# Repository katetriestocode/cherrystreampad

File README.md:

# cherrystreampad
hackclub project!

This is my cherrystreampad!
(cherry when i paint it LOL)
its used as a streampad/deck, with handy dandy tools such as volume control and app shortcuts!
I made this caus stream decks are super expensive, and this was so fun to do!!!

It has 6 keys, and OLED teeny screen and a rotary encoder!

# This is the PCB:

# And this is the schematic:

# this is (just) the case: 

# BOM parts

- 6x Cherry MX Switches
- 6x White Keycaps
- 4x M3x16mm screws
- 1x 0.91" 128x32 OLED Display
- 1x EC11 Rotary Encoder
- 1x XIAO RP2040
- 1x Case (2 printed parts)

<shark missing :(>

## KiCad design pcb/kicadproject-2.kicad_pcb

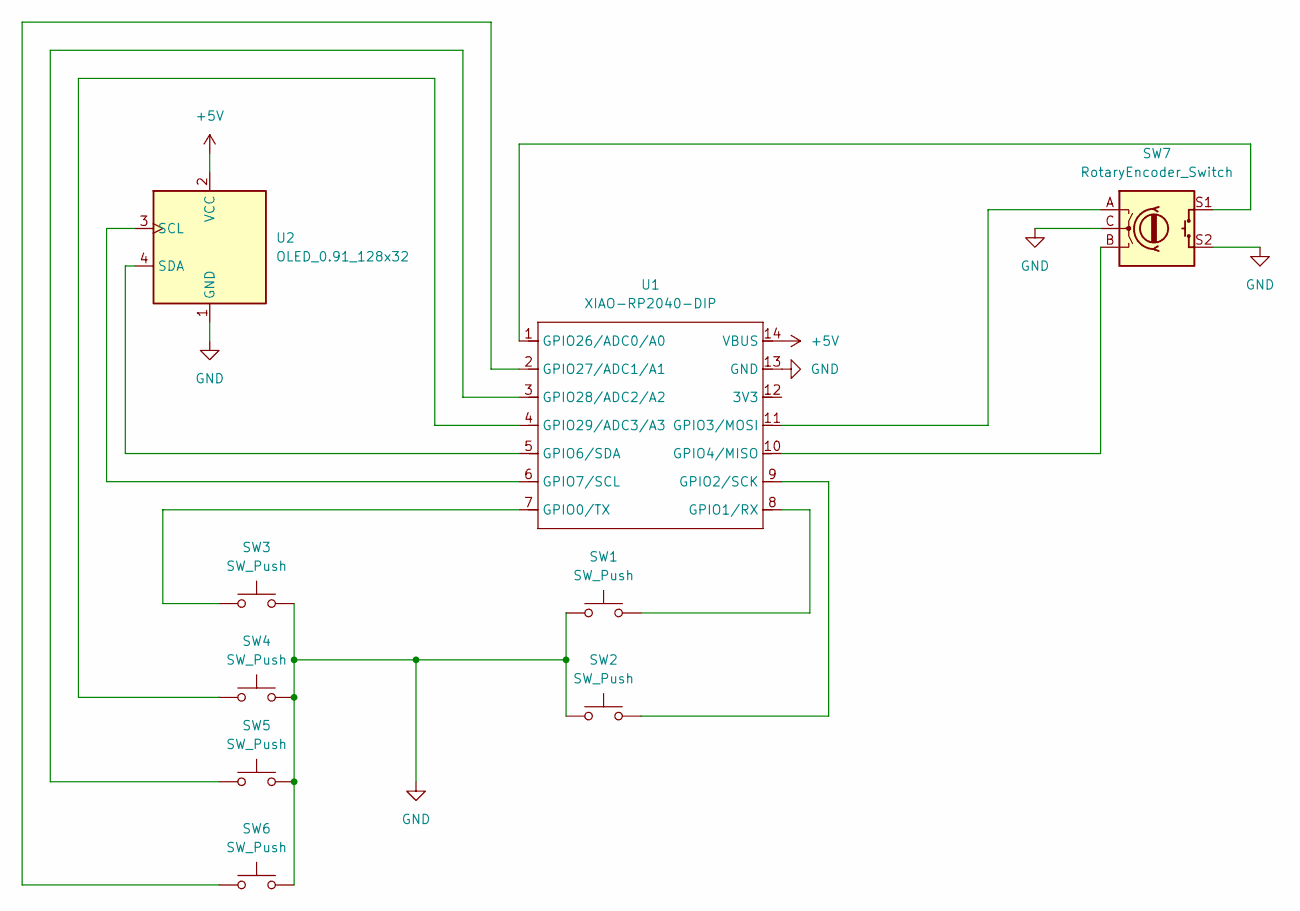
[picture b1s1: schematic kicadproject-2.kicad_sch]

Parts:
SW1, SW2, SW3, SW4, SW5, SW6: SW_Push; SW_Cherry_MX_1.00u_PCB
SW7: RotaryEncoder_Switch; RotaryEncoder_Alps_EC11E-Switch_Vertical_H20mm
U1: XIAO-RP2040-DIP
U2: OLED_0.91_128x32

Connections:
+5V: U1.14 (VBUS), U2.2 (VCC)
GND: SW1.1, SW2.1, SW3.2, SW4.2, SW5.2, SW6.2, SW7.C, SW7.S2, U1.13 (GND), U2.1 (GND)
unnamed: SW3.1, U1.7 (GPIO0/TX)
unnamed: SW1.2, U1.8 (GPIO1/RX)
unnamed: SW2.2, U1.9 (GPIO2/SCK)
unnamed: SW7.A, U1.11 (GPIO3/MOSI)
unnamed: SW7.B, U1.10 (GPIO4/MISO)
unnamed: U1.5 (GPIO6/SDA), U2.4 (SDA)
unnamed: U1.6 (GPIO7/SCL), U2.3 (SCL)
unnamed: SW7.S1, U1.1 (GPIO26/ADC0/A0)
unnamed: SW6.1, U1.2 (GPIO27/ADC1/A1)
unnamed: SW5.1, U1.3 (GPIO28/ADC2/A2)
unnamed: SW4.1, U1.4 (GPIO29/ADC3/A3)

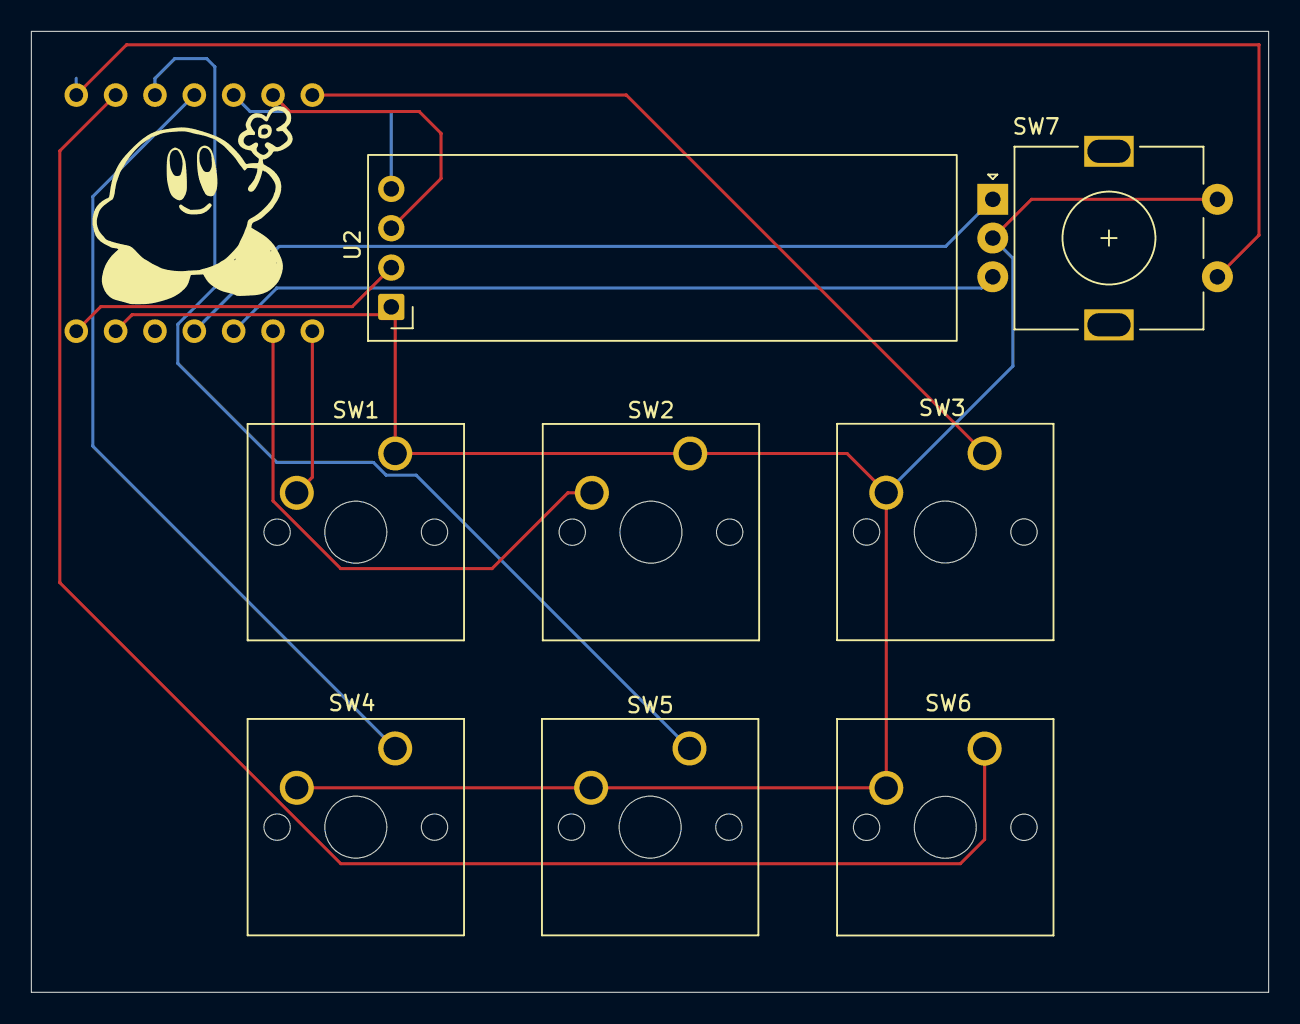
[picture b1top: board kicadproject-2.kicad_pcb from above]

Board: 2 copper layers, 79.9 x 62.0 mm, 10 parts (1 on the bottom side), 13 nets.

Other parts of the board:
logo: LOGO; kirbysmaller

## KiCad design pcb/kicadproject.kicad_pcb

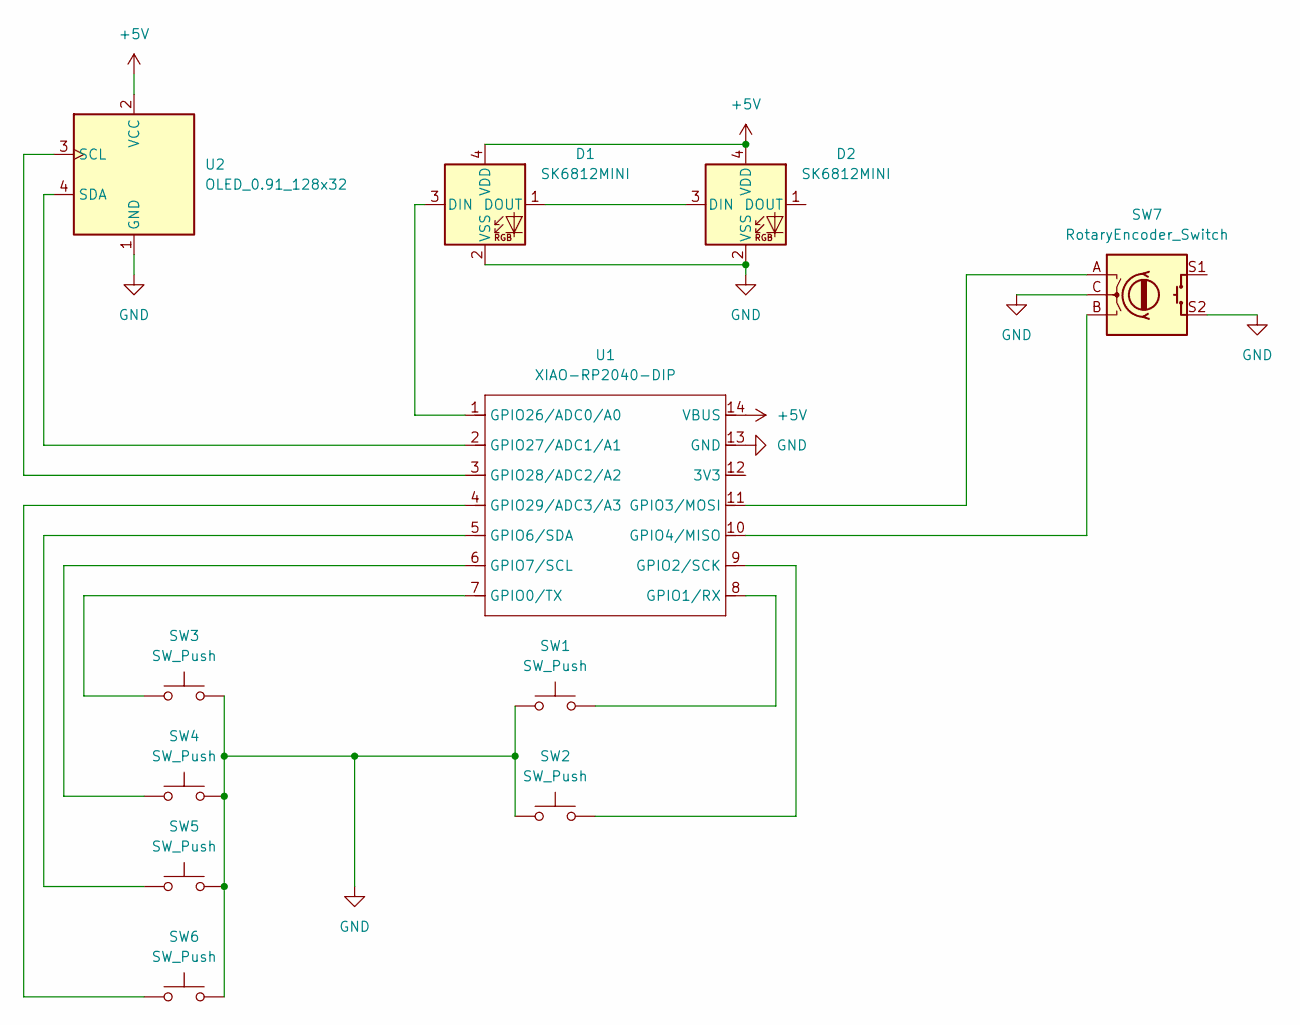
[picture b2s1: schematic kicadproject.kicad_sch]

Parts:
D1, D2: SK6812MINI; LED_SK6812MINI_PLCC4_3.5x3.5mm_P1.75mm
SW1, SW2, SW3, SW4, SW5, SW6: SW_Push; SW_Cherry_MX_1.00u_PCB
SW7: RotaryEncoder_Switch; RotaryEncoder_Alps_EC11E-Switch_Vertical_H20mm
U1: XIAO-RP2040-DIP
U2: OLED_0.91_128x32

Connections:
+5V: D1.4 (VDD), D2.4 (VDD), U1.14 (VBUS), U2.2 (VCC)
GND: D1.2 (VSS), D2.2 (VSS), SW1.1, SW2.1, SW3.2, SW4.2, SW5.2, SW6.2, SW7.C, SW7.S2, U1.13 (GND), U2.1 (GND)
unnamed: D1.3 (DIN), U1.1 (GPIO26/ADC0/A0)
unnamed: D1.1 (DOUT), D2.3 (DIN)
unnamed: SW3.1, U1.7 (GPIO0/TX)
unnamed: SW1.2, U1.8 (GPIO1/RX)
unnamed: SW2.2, U1.9 (GPIO2/SCK)
unnamed: SW7.A, U1.11 (GPIO3/MOSI)
unnamed: SW7.B, U1.10 (GPIO4/MISO)
unnamed: SW5.1, U1.5 (GPIO6/SDA)
unnamed: SW4.1, U1.6 (GPIO7/SCL)
unnamed: U1.2 (GPIO27/ADC1/A1), U2.4 (SDA)
unnamed: U1.3 (GPIO28/ADC2/A2), U2.3 (SCL)
unnamed: SW6.1, U1.4 (GPIO29/ADC3/A3)

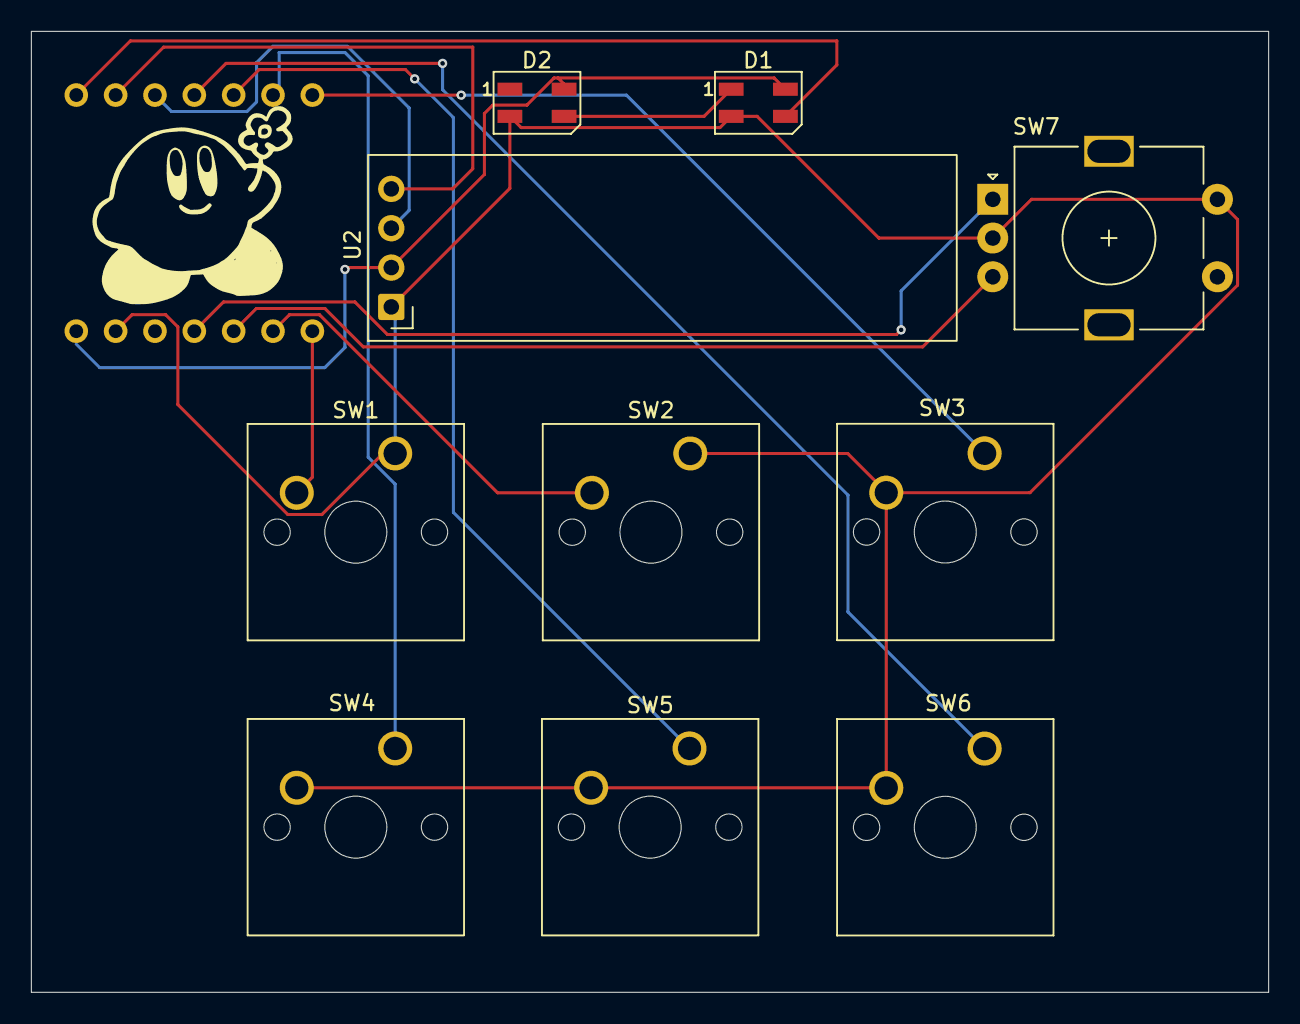
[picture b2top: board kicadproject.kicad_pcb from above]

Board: 2 copper layers, 79.9 x 62.0 mm, 12 parts (1 on the bottom side), 14 nets.

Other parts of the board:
logo: LOGO; kirbysmaller

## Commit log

2026-03-05 first set
2026-03-05 cadupload
2026-03-06 mainscript
2026-03-06 moved
2026-03-07 fix?
2026-03-07 dangit
2026-03-07 morereadme
2026-03-07 fixedshork
2026-03-07 no shark ig
2026-03-07 urgh spacing
2026-03-07 added image
    E.
2026-03-09 removedledaddedswitch
2026-03-09 pythonfix
2026-03-09 smallfix
2026-03-09 smallerfix
2026-03-09 urgh
2026-03-09 newphoto
2026-03-09 FLOWERS
2026-03-10 massiveupdate
2026-03-10 Enhanced README
2026-03-10 fixedpcb
2026-03-10 firmwarefix
2026-03-10 Update images for PCB, schematic, and case in README
